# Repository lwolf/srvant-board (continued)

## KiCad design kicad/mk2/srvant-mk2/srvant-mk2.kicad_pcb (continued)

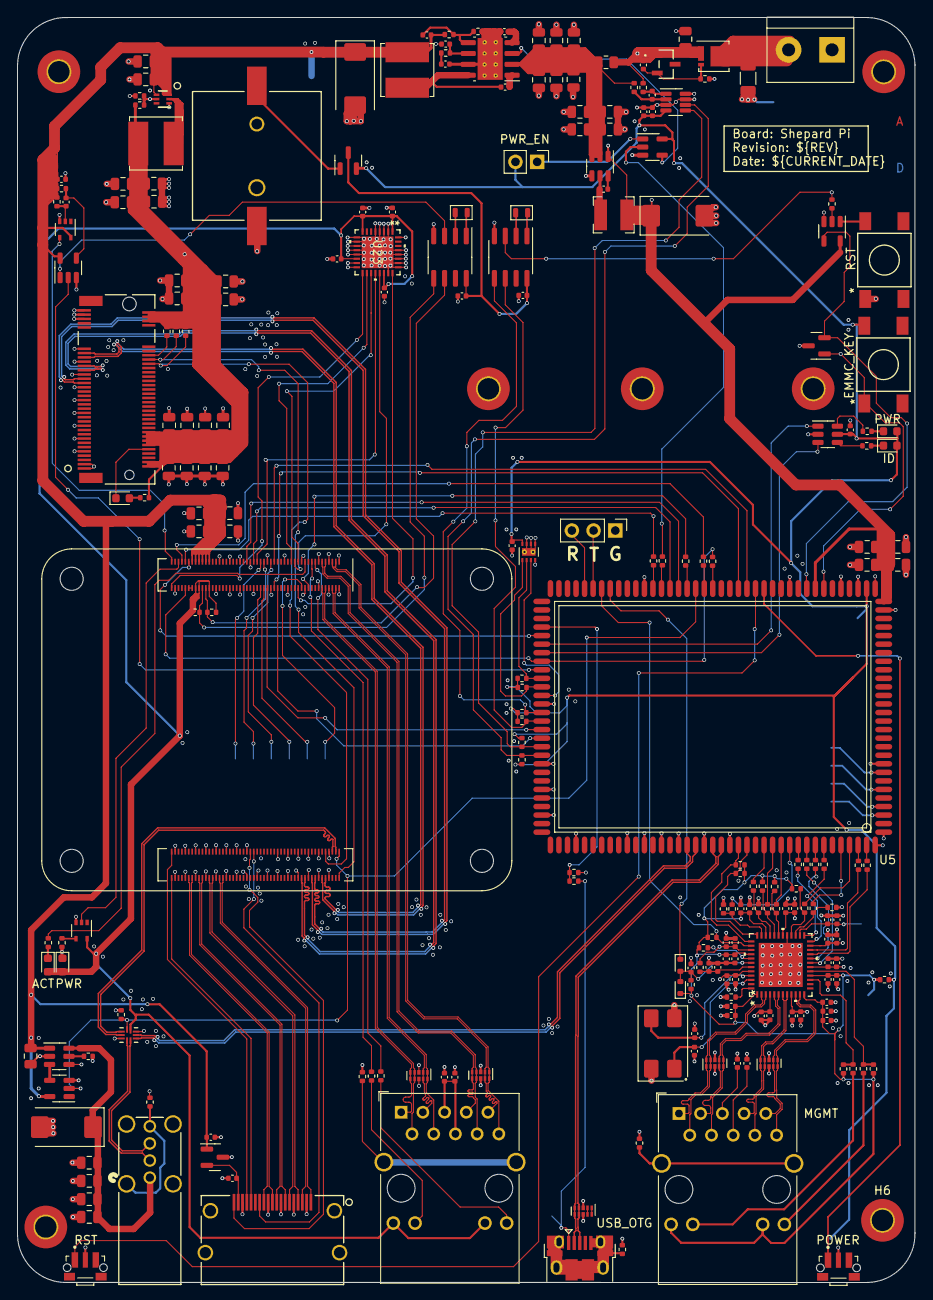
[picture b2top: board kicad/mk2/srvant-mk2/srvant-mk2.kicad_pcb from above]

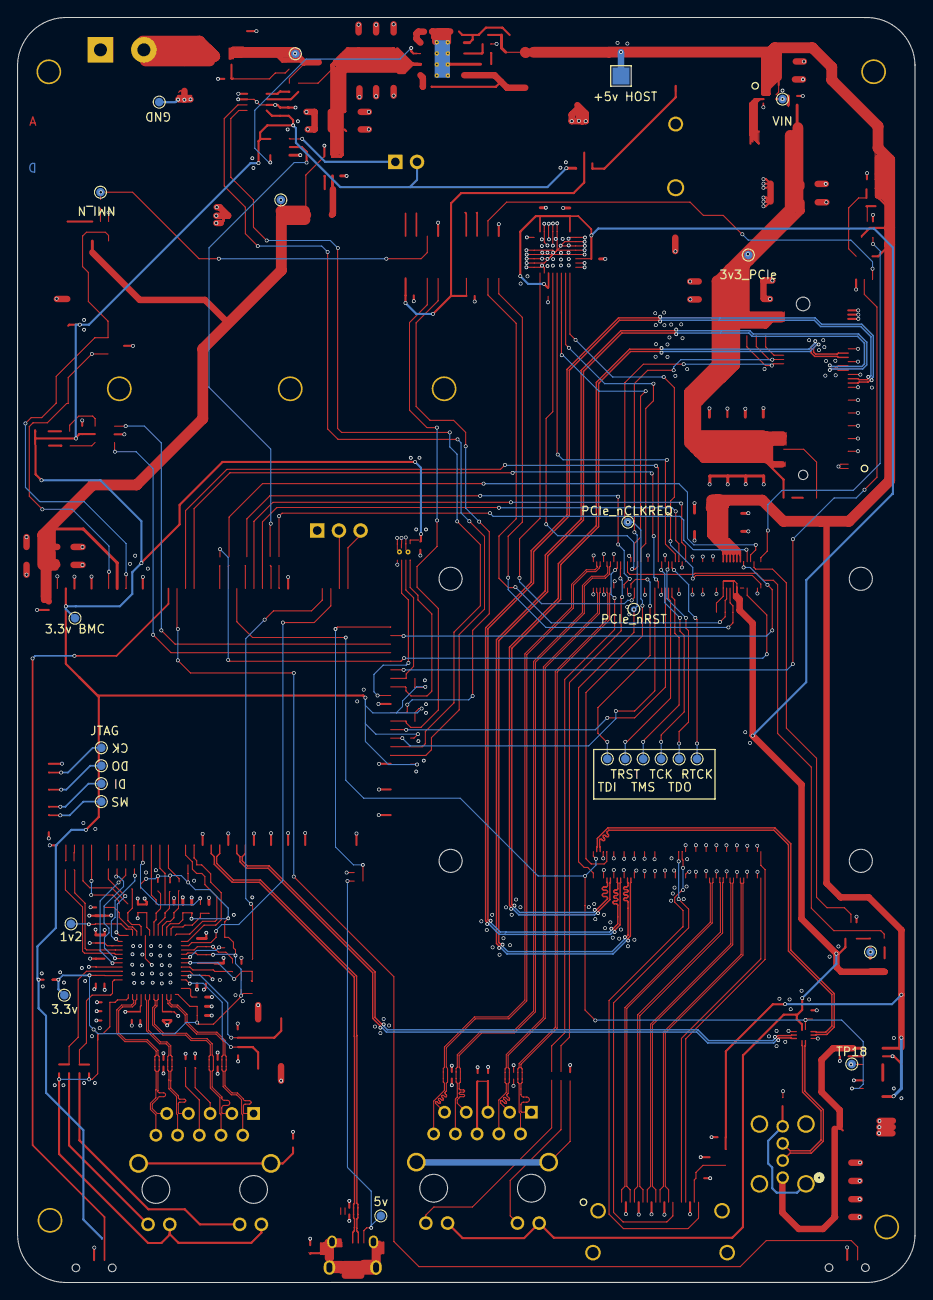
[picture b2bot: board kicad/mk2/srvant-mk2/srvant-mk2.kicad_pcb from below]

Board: 4 copper layers, 105.0 x 148.0 mm, 266 parts (25 on the bottom side), 206 nets.

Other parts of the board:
R3: 2K2; R_0402_1005Metric

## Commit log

2021-07-14 Add rev01 files
    Add datasheets, inspliration links, renders and kicad sources
2021-07-19 Update readme in the inspirations section
2022-07-26 Backlink to CADLAB.io has been added.
2022-08-07 save state
    save state to try to migrate to kicad in linux
2023-06-20 add design guildline
2023-06-24 fresh start
2023-07-31 work on schematics
    * add power rail
    * import CM4 related part
    * design most of the BMC-PHY part
    * create new library/footprint for rp t113-s3 SOM
2023-08-01 more progress
2023-08-01 add datasheets, cleanup ci config
2023-11-25 save state
2023-12-17 mostly wired, impedance control, etc
    Repositioned most of the components. Set impedance control based
    on jlcpcb calculator.
    Need to:
    * reposition ethernet port to allow mounting hole.
    * move power socket lower, reduce board size
    * fix the rest of DRC errors.
2023-12-19 remove old mk1 version
2023-12-19 trying to make CI work
2023-12-19 change cache_dir for `basic_diff_sch` which fails in CI
    as found at https://github.com/INTI-CMNB/KiBot/discussions/312
2023-12-19 resolve a bunch of DRC issues
2023-12-22 disable basic_dif_sch
2023-12-22 change jack footprint, re-route minor thing.
2023-12-22 bump artifact-upload image
2023-12-22 resolve some of the warnings
2023-12-22 comment out svg generation
2023-12-22 fix descriptions, add 3dmodels.
2023-12-27 replace power jack, change board dimentions, small fixes
2023-12-27 readme
2023-12-29 add more 3d models
2023-12-29 add more 3d models, add layer indication, update readme
2023-12-29 add rp-t113-s3 datasheets (cn), make CI happier
2023-12-29 Fix wrong capacitors placement of +5v_BMC, fix DRC issues
2023-12-29 Replace filled zones with lots of traces
2023-12-29 fix another filling place, render individual layers as pdfs/svgs
2024-01-02 small fixes
    * fix unconnected vias near M2
    * fix missing resistors near rpi i2c
    * silkscreen fixes
2024-01-02 rework CI workflows
    Separate CI workflows.
    Run basic DRC and DIFFs on every commit.
    Run full set of actions including 3d and manufacture packages on tags
    only.
2024-01-02 increase verbosity level for kibot
2024-01-02 fix 3d models. again
    Once again assign all the 3d models to the components.
2024-01-02 Add an exception to the DRC about footprint mismatch
    In Kicad7, when you add a 3d model to the footprint that doesn't have
    one, warning is being generated.
    Proper way will be to make a copy of the footprint and add the model
    there.
    Ignore the warning for now.
    ref: https://forum.kicad.info/t/footprint-does-not-match-copy-in-library-when-3d-model-is-added/45176/3
2024-01-27 reroute diff pairs
    Reroute all diff pairs after another run with the jlcpcb calculator.
2024-01-31 small changes to routing
2024-01-31 experiment with kibot
2024-01-31 disable diffs for now
2024-01-31 disable diffs on releases as well
2024-02-11 lot's of small updates
    * fix the quartz footprint
    * fix wrong inductor in pcie power unit
    * fix lots of descriptions,uids
2024-02-11 fix drc
2024-02-11 fix variable substitution
2024-02-14 normalize border size
2024-02-17 add jtag pads, improve power lines
2024-02-18 pre-production: fix silkscreens
2024-03-13 Fixes after manufacturing
    * Change footprint for the VIN capacitors. 10uf was supposed to be 0804
    not 0402. That required repositioning of both power converters.
    * Fix PWR_EN pin override (2.54mm instead of 1.0)
    * Change resistor values in voltage divider of AP64501SP. Values taken
    from RPI carrier board produce wrong voltage (~3.6v instead of 5v).
    * Add silkscreen labels around the LEDs.
2024-06-19 bmc usb id pin fix
    ID pin is supposed to be unconnected on a peripheral device.
    Connect usb_detect pin to VBUS using voltage divider (like in cm4 doc).
2024-06-19 bump kicad in ci
2025-01-03 redesign for the next version
2025-01-04 state
2025-01-08 v1.5 draft
2025-01-08 bump kicad CI image, temp disable erc
2025-01-08 generate 3d on each build
2025-01-18 fix github workflows
2025-08-24 change kibot to use nerdctl, stop tracking lck files
2025-08-24 act-based local runner with makefile
2025-08-24 remove 3d steps from the quick run
2025-08-24 add 3d steps as a separate workflow
2025-08-26 uncomment diff rules, fix act to not run 3d steps
2025-08-26 allow running diff against arbitrary pair of commits
2025-08-26 reduce logging, release entry in make, diff in release
2025-08-26 bump kibot version, add untested kicost
2025-09-28 cm dev board
2025-11-09 state of the cm4(5), manufactured revision
